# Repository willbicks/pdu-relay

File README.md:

# PDU Relay Module

This PDU relay is intended to be retrofit into a standard 19" rack mount PDU, and allows for any subsection of the outputs to be turned on or off based on an external isolated logic input. It provides a relay that energizes the live rail of the PDU only when the logic input is held low, and de-energizes them otherwise. This makes the logic input suitable for any dry contact or open collector output that can sink a few milliamps of current.

In my case, I am using this module in a JG JR PDU to switch on audio amplifiers when a Biamp Tesira DSP detects audio input, and then automatically switch them back off after a period of inactivity to conserve power.

## Specifications

### Electrical Specifications

This power supply and relay in this module are rated to support:

- 120 - 240 VAC input at 50-60Hz
- 16 A AC load switching (resistive)

The AC input / output terminals are 0.25" x 0.032" spade terminals.

The logic input is a 2.54mm pitch 2-pin screw terminal. Pin 1 is an AC isolated ground, while pin 2 is the active low logic input. To close the relay, pin 2 should be pulled low relative to the ground terminal. Total current draw from the logic input is less than 1 mA.

### Mechanical Specifications

The assembled module is 55 mm x 40 mm x ~20mm. It has 4 holes for M3 screws that are 47 mm x 32 mm between centers as shown below.

## Source Usage

This repository contains a KiCAD 8.0.0 project with the schematic and PCB layout for the PDU relay module. Gerber files, a BOM, and PDFs of the schematic and PCB layout are available in the [releases section of the repository](https://www.github.com/willbicks/pdu-relay/releases).

## Electrical Safety

This unit is intended for reference and evaluation and has not been tested nor certified by any safety agency. It is the responsibility of the user to ensure that the final product meets all applicable safety standards and regulations.

In addition to ensuring that this design meets all applicable safety standards and regulations, the following basic precautions should be taken when installing and using this module:

- The module should be securely mounted in a suitable metallic, grounded enclosure.
- The module should be installed downstream of a suitable overcurrent protection device rated for no more than 16 A.
- The switched terminals should be connected to the live rail of the PDU, and the PDU should have an appropriately polarized plug.
- Connections to and from the module should be made with suitable wire and connectors rated for the intended current and voltage, and which are insulated from accidental electrical contact.

## License

Copyright Will Bicks 2024.

This source describes Open Hardware and is licensed under the CERN-OHLW v2
You may redistribute and modify this documentation and make products
using it under the terms of the CERN-OHL-W v2 (https:/cern.ch/cern-ohl).

This documentation is distributed WITHOUT ANY EXPRESS OR IMPLIED
WARRANTY, INCLUDING OF MERCHANTABILITY, SATISFACTORY QUALITY
AND FITNESS FOR A PARTICULAR PURPOSE. Please see the CERN-OHL-W v2
for applicable conditions.

Source location: https://www.github.com/willbicks/pdu-relay

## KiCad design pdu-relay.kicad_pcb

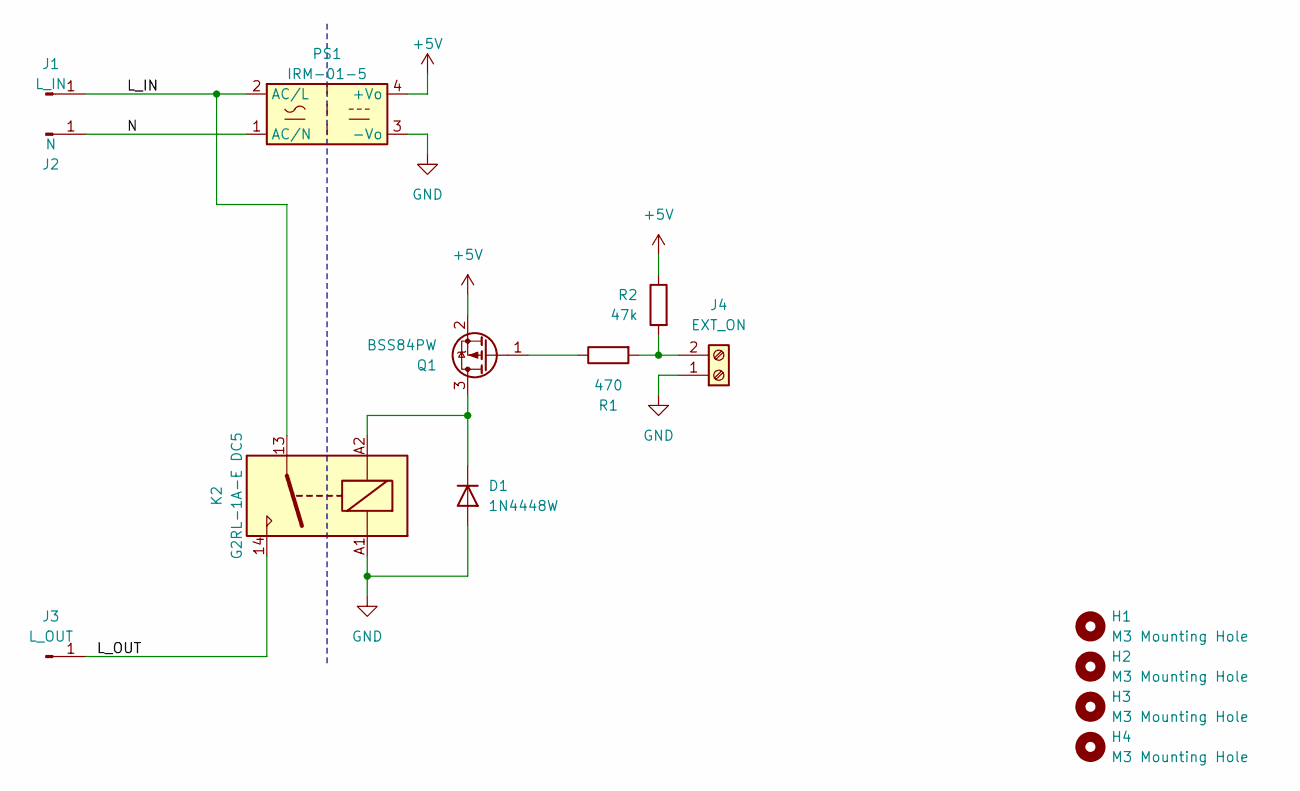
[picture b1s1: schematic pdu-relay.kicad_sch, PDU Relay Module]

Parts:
D1: 1N4448W; D_SOD-123F
H1, H2, H3, H4: M3 Mounting Hole; MountingHole_3.2mm_M3
J1: L_IN; Keystone_4966
J2: N; Keystone_4966
J3: L_OUT; Keystone_4966
J4: EXT_ON; TerminalBlock_TE_282834-2_1x02_P2.54mm_Horizontal
K2: G2RL-1A-E DC5; Relay_SPST_Omron_G2RL-1A-E
PS1: IRM-01-5; Converter_ACDC_MeanWell_IRM-02-xx_THT
Q1: BSS84PW; SOT-323_SC-70
R1: 470; R_0805_2012Metric
R2: 47k; R_0805_2012Metric

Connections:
+5V: PS1.4 (+Vo), Q1.2 (S), R2.1
/L_IN: J1.1, K2.13, PS1.2 (AC/L)
/L_OUT: J3.1, K2.14
/N: J2.1, PS1.1 (AC/N)
GND: D1.2 (A), J4.1, K2.A1, PS1.3 (-Vo)
unnamed: D1.1 (K), K2.A2, Q1.3 (D)
unnamed: J4.2, R1.2, R2.2
unnamed: Q1.1 (G), R1.1

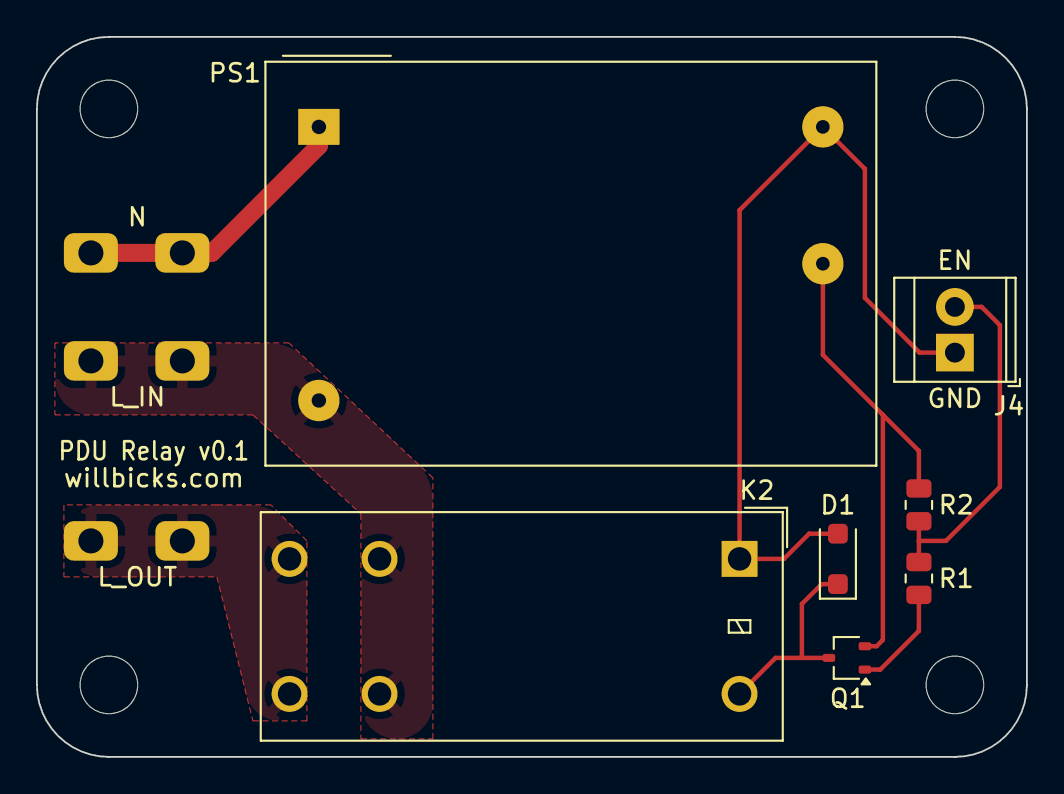
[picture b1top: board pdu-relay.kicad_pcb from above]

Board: 2 copper layers, 55.0 x 40.0 mm, 14 parts (0 on the bottom side), 8 nets.

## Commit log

2024-02-25 Initial commit.
2024-02-25 Add PDU Relay Module v0.1.
2024-02-25 Add additional dimensions to PCB User.1
2024-02-25 Expand README
2024-02-25 Rearrange L_OUT for rectangular hole pattern and add 3D models.
2024-02-25 Add *.lck lock files to gitignore
2024-02-25 Add 3D model for spade terminals
2024-02-25 Update fabrication outputs, exclude non-parts from BOM.
2024-02-25 Add gitattributes to detect KiCAD files with Linguist.
